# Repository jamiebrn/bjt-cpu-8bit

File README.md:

# BJT 8 bit CPU

Designing and (hopefully) building a custom 8 bit CPU with NPN bipolar junction transistors

The [ISA](specification.txt) is fully working and implemented in [logisim](logisim-prototypes/cpu-rebuild.circ), as shown:

I have also written an [assembler](assembler/assembler.cpp), and am working on the [emulator](emulator/) (functional but some graphics issues).

A barebones [standard library](programs/stdlib/) is also implemented.

## Physical build
I have [prototyped the ALU on breadboards](images/8bit-alu-labelled.png), and have started [working on PCB components](images/pcb-8bit-reg-v3-refined.png).

### "Just use ICs"
No

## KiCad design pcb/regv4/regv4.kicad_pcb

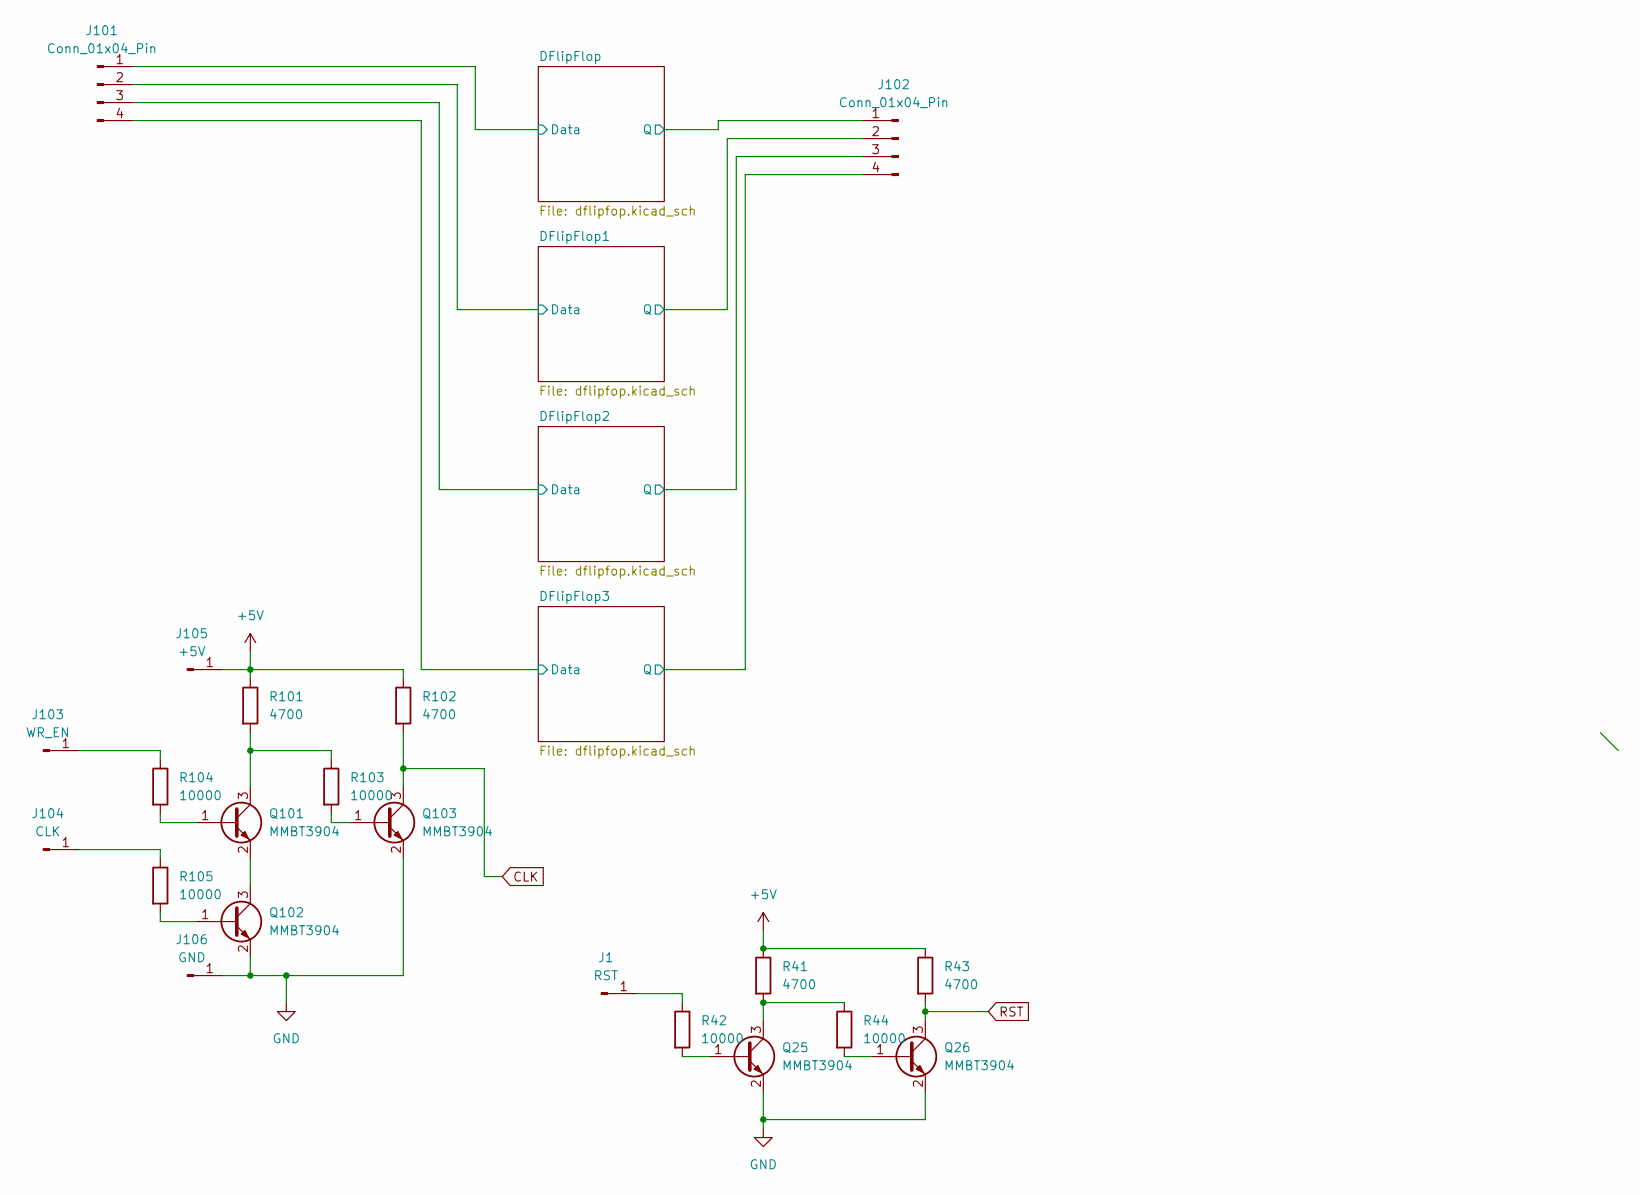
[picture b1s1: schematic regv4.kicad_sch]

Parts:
J1: RST; PinHeader_1x01_P2.54mm_Vertical
J101, J102: Conn_01x04_Pin; PinHeader_1x04_P2.54mm_Vertical
J103: WR_EN; PinHeader_1x01_P2.54mm_Vertical
J104: CLK; PinHeader_1x01_P2.54mm_Vertical
J105: +5V; PinHeader_1x01_P2.54mm_Vertical
J106: GND; PinHeader_1x01_P2.54mm_Vertical
Q25, Q26, Q101, Q102, Q103: MMBT3904; SOT-23
R41, R43, R101, R102: 4700; R_0805_2012Metric
R42, R44, R103, R104, R105: 10000; R_0805_2012Metric

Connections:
+5V: J105.1, R41.1, R43.1, R101.1, R102.1; also elsewhere on the board
/DFlipFlop1/Data: J101.2; also elsewhere on the board
/DFlipFlop1/Q: J102.2; also elsewhere on the board
/DFlipFlop2/Data: J101.3; also elsewhere on the board
/DFlipFlop2/Q: J102.3; also elsewhere on the board
/DFlipFlop3/Data: J101.4; also elsewhere on the board
/DFlipFlop3/Q: J102.4; also elsewhere on the board
/DFlipFlop/Data: J101.1; also elsewhere on the board
/DFlipFlop/Q: J102.1; also elsewhere on the board
CLK: Q103.3 (C), R102.2; also elsewhere on the board
GND: J106.1, Q25.2 (E), Q26.2 (E), Q102.2 (E), Q103.2 (E); also elsewhere on the board
unnamed: J1.1, R42.1
unnamed: J103.1, R104.1
unnamed: J104.1, R105.1
unnamed: Q25.1 (B), R42.2
unnamed: Q25.3 (C), R41.2, R44.1
unnamed: Q26.1 (B), R44.2
unnamed: Q101.1 (B), R104.2
unnamed: Q101.3 (C), R101.2, R103.1
unnamed: Q101.2 (E), Q102.3 (C)
unnamed: Q102.1 (B), R105.2
unnamed: Q103.1 (B), R103.2
RST: Q26.3 (C), R43.2; also elsewhere on the board

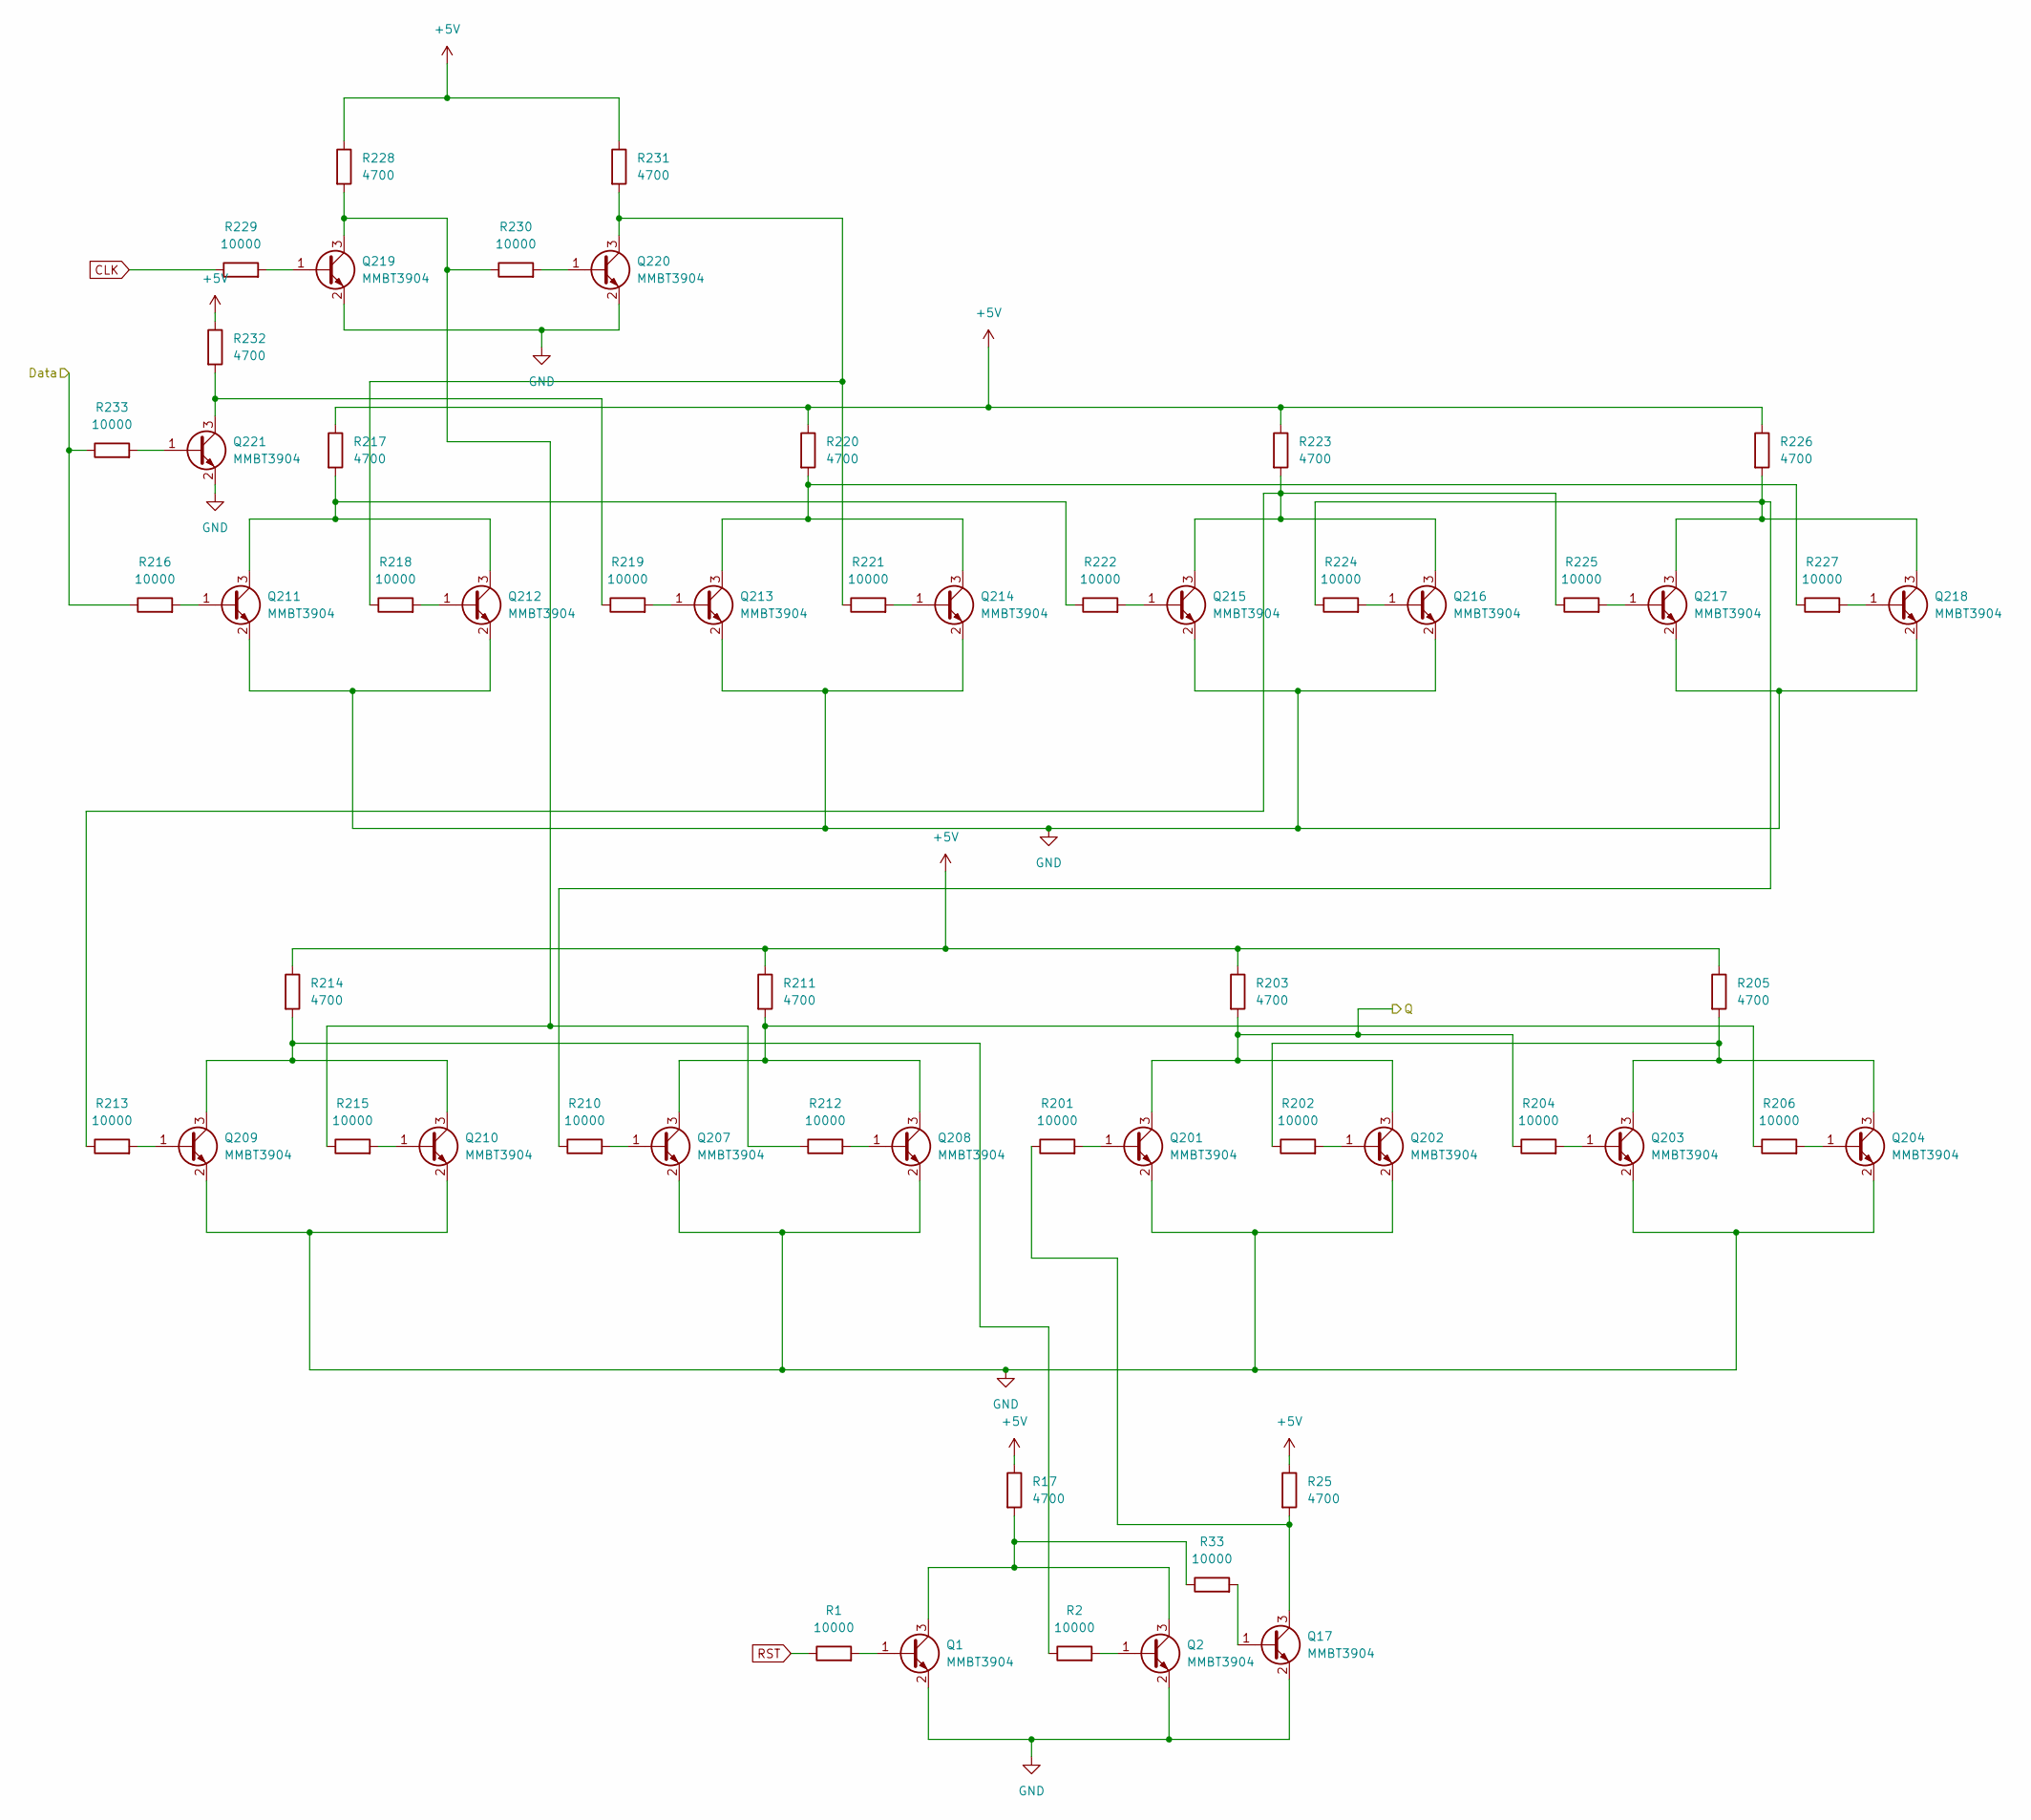
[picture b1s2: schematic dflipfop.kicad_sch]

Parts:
Q1, Q2, Q17, Q201, Q202, Q203, Q204, Q207, Q208, Q209, Q210, Q211, Q212, Q213, Q214, Q215, Q216, Q217, Q218, Q219, Q220, Q221: MMBT3904; SOT-23
R1, R2, R33, R201, R202, R204, R206, R210, R212, R213, R215, R216, R218, R219, R221, R222, R224, R225, R227, R229, R230, R233: 10000; R_0805_2012Metric
R17, R25, R203, R205, R211, R214, R217, R220, R223, R226, R228, R231, R232: 4700; R_0805_2012Metric

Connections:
+5V: R17.1, R25.1, R203.1, R205.1, R211.1, R214.1, R217.1, R220.1, R223.1, R226.1, R228.1, R231.1, R232.1; also elsewhere on the board
/DFlipFlop/Data: R216.1, R233.1; also elsewhere on the board
/DFlipFlop/Q: Q201.3 (C), Q202.3 (C), R203.2, R204.1; also elsewhere on the board
CLK: R229.1; also elsewhere on the board
GND: Q1.2 (E), Q2.2 (E), Q17.2 (E), Q201.2 (E), Q202.2 (E), Q203.2 (E), Q204.2 (E), Q207.2 (E), Q208.2 (E), Q209.2 (E), Q210.2 (E), Q211.2 (E), Q212.2 (E), Q213.2 (E), Q214.2 (E), Q215.2 (E), Q216.2 (E), Q217.2 (E), Q218.2 (E), Q219.2 (E), Q220.2 (E), Q221.2 (E); also elsewhere on the board
unnamed: Q1.1 (B), R1.2
unnamed: Q1.3 (C), Q2.3 (C), R17.2, R33.1
unnamed: Q2.1 (B), R2.2
unnamed: Q17.1 (B), R33.2
unnamed: Q17.3 (C), R25.2, R201.1
unnamed: Q201.1 (B), R201.2
unnamed: Q202.1 (B), R202.2
unnamed: Q203.1 (B), R204.2
unnamed: Q203.3 (C), Q204.3 (C), R202.1, R205.2
unnamed: Q204.1 (B), R206.2
unnamed: Q207.1 (B), R210.2
unnamed: Q207.3 (C), Q208.3 (C), R206.1, R211.2
unnamed: Q208.1 (B), R212.2
unnamed: Q209.1 (B), R213.2
unnamed: Q209.3 (C), Q210.3 (C), R2.1, R214.2
unnamed: Q210.1 (B), R215.2
unnamed: Q211.1 (B), R216.2
unnamed: Q211.3 (C), Q212.3 (C), R217.2, R222.1
unnamed: Q212.1 (B), R218.2
unnamed: Q213.1 (B), R219.2
unnamed: Q213.3 (C), Q214.3 (C), R220.2, R227.1
unnamed: Q214.1 (B), R221.2
unnamed: Q215.1 (B), R222.2
unnamed: Q215.3 (C), Q216.3 (C), R213.1, R223.2, R225.1
unnamed: Q216.1 (B), R224.2
unnamed: Q217.1 (B), R225.2
unnamed: Q217.3 (C), Q218.3 (C), R210.1, R224.1, R226.2
unnamed: Q218.1 (B), R227.2
unnamed: Q219.1 (B), R229.2
unnamed: Q219.3 (C), R212.1, R215.1, R228.2, R230.1
unnamed: Q220.1 (B), R230.2
unnamed: Q220.3 (C), R218.1, R221.1, R231.2
unnamed: Q221.1 (B), R233.2
unnamed: Q221.3 (C), R219.1, R232.2
RST: R1.1; also elsewhere on the board

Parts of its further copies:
Q3, Q4, Q5, Q6, Q7, Q8, Q18, Q19, Q20, Q301, Q302, Q303, Q304, Q305, Q306, Q307, Q308, Q309, Q310, Q311, Q312, Q313, Q314, Q315, Q316, Q317, Q318, Q319, Q401, Q402, Q403, Q404, Q405, Q406, Q407, Q408, Q409, Q410, Q411, Q412, Q413, Q414, Q415, Q416, Q417, Q418, Q419, Q501, Q502, Q503, Q504, Q505, Q506, Q507, Q508, Q509, Q510, Q511, Q512, Q513, Q514, Q515, Q516, Q517, Q518, Q519: MMBT3904; SOT-23
R3, R4, R5, R6, R7, R8, R34, R35, R36, R301, R302, R303, R305, R309, R310, R311, R312, R314, R317, R318, R319, R320, R323, R324, R325, R326, R329, R330, R401, R402, R403, R405, R409, R410, R411, R412, R414, R417, R418, R419, R420, R423, R424, R425, R426, R429, R430, R501, R502, R503, R505, R509, R510, R511, R512, R514, R517, R518, R519, R520, R523, R524, R525, R526, R529, R530: 10000; R_0805_2012Metric
R18, R19, R20, R26, R27, R28, R304, R306, R307, R308, R313, R315, R316, R321, R322, R327, R328, R404, R406, R407, R408, R413, R415, R416, R421, R422, R427, R428, R504, R506, R507, R508, R513, R515, R516, R521, R522, R527, R528: 4700; R_0805_2012Metric

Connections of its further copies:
+5V: R18.1, R19.1, R20.1, R26.1, R27.1, R28.1, R304.1, R306.1, R307.1, R308.1, R313.1, R315.1, R316.1, R321.1, R322.1, R327.1, R328.1, R404.1, R406.1, R407.1, R408.1, R413.1, R415.1, R416.1, R421.1, R422.1, R427.1, R428.1, R504.1, R506.1, R507.1, R508.1, R513.1, R515.1, R516.1, R521.1, R522.1, R527.1, R528.1; also elsewhere on the board
/DFlipFlop1/Data: R301.1, R303.1; also elsewhere on the board
/DFlipFlop1/Q: Q312.3 (C), Q314.3 (C), R321.2, R325.1; also elsewhere on the board
/DFlipFlop2/Data: R401.1, R403.1; also elsewhere on the board
/DFlipFlop2/Q: Q412.3 (C), Q414.3 (C), R421.2, R425.1; also elsewhere on the board
/DFlipFlop3/Data: R501.1, R503.1; also elsewhere on the board
/DFlipFlop3/Q: Q512.3 (C), Q514.3 (C), R521.2, R525.1; also elsewhere on the board
CLK: R305.1, R405.1, R505.1; also elsewhere on the board
GND: Q3.2 (E), Q4.2 (E), Q5.2 (E), Q6.2 (E), Q7.2 (E), Q8.2 (E), Q18.2 (E), Q19.2 (E), Q20.2 (E), Q301.2 (E), Q302.2 (E), Q303.2 (E), Q304.2 (E), Q305.2 (E), Q306.2 (E), Q307.2 (E), Q308.2 (E), Q309.2 (E), Q310.2 (E), Q311.2 (E), Q312.2 (E), Q313.2 (E), Q314.2 (E), Q315.2 (E), Q316.2 (E), Q317.2 (E), Q318.2 (E), Q319.2 (E), Q401.2 (E), Q402.2 (E), Q403.2 (E), Q404.2 (E), Q405.2 (E), Q406.2 (E), Q407.2 (E), Q408.2 (E), Q409.2 (E), Q410.2 (E), Q411.2 (E), Q412.2 (E), Q413.2 (E), Q414.2 (E), Q415.2 (E), Q416.2 (E), Q417.2 (E), Q418.2 (E), Q419.2 (E), Q501.2 (E), Q502.2 (E), Q503.2 (E), Q504.2 (E), Q505.2 (E), Q506.2 (E), Q507.2 (E), Q508.2 (E), Q509.2 (E), Q510.2 (E), Q511.2 (E), Q512.2 (E), Q513.2 (E), Q514.2 (E), Q515.2 (E), Q516.2 (E), Q517.2 (E), Q518.2 (E), Q519.2 (E); also elsewhere on the board
unnamed: Q3.1 (B), R3.2
unnamed: Q3.3 (C), Q4.3 (C), R18.2, R34.1
unnamed: Q4.1 (B), R4.2
unnamed: Q5.1 (B), R5.2
unnamed: Q5.3 (C), Q6.3 (C), R19.2, R35.1
unnamed: Q6.1 (B), R6.2
unnamed: Q7.1 (B), R7.2
unnamed: Q7.3 (C), Q8.3 (C), R20.2, R36.1
unnamed: Q8.1 (B), R8.2
unnamed: Q18.1 (B), R34.2
unnamed: Q18.3 (C), R26.2, R319.1
unnamed: Q19.1 (B), R35.2
unnamed: Q19.3 (C), R27.2, R419.1
unnamed: Q20.1 (B), R36.2
unnamed: Q20.3 (C), R28.2, R519.1
unnamed: Q301.1 (B), R302.2
unnamed: Q301.3 (C), Q305.3 (C), R4.1, R306.2
unnamed: Q302.1 (B), R301.2
unnamed: Q302.3 (C), R304.2, R314.1
unnamed: Q303.1 (B), R303.2
unnamed: Q303.3 (C), Q306.3 (C), R307.2, R320.1
unnamed: Q304.1 (B), R305.2
unnamed: Q304.3 (C), R308.2, R309.1, R311.1, R317.1
unnamed: Q305.1 (B), R309.2
unnamed: Q306.1 (B), R310.2
unnamed: Q307.1 (B), R311.2
unnamed: Q307.3 (C), R310.1, R313.2, R318.1
unnamed: Q308.1 (B), R312.2
unnamed: Q308.3 (C), Q310.3 (C), R315.2, R329.1
unnamed: Q309.1 (B), R314.2
unnamed: Q309.3 (C), Q311.3 (C), R316.2, R330.1
unnamed: Q310.1 (B), R317.2
unnamed: Q311.1 (B), R318.2
unnamed: Q312.1 (B), R319.2
unnamed: Q313.1 (B), R320.2
unnamed: Q313.3 (C), Q315.3 (C), R302.1, R322.2, R326.1
unnamed: Q314.1 (B), R323.2
unnamed: Q315.1 (B), R324.2
unnamed: Q316.1 (B), R325.2
unnamed: Q316.3 (C), Q318.3 (C), R323.1, R327.2
unnamed: Q317.1 (B), R326.2
unnamed: Q317.3 (C), Q319.3 (C), R312.1, R324.1, R328.2
unnamed: Q318.1 (B), R329.2
unnamed: Q319.1 (B), R330.2
unnamed: Q401.1 (B), R402.2
unnamed: Q401.3 (C), Q405.3 (C), R6.1, R406.2
unnamed: Q402.1 (B), R401.2
unnamed: Q402.3 (C), R404.2, R414.1
unnamed: Q403.1 (B), R403.2
unnamed: Q403.3 (C), Q406.3 (C), R407.2, R420.1
unnamed: Q404.1 (B), R405.2
unnamed: Q404.3 (C), R408.2, R409.1, R411.1, R417.1
unnamed: Q405.1 (B), R409.2
unnamed: Q406.1 (B), R410.2
unnamed: Q407.1 (B), R411.2
unnamed: Q407.3 (C), R410.1, R413.2, R418.1
unnamed: Q408.1 (B), R412.2
unnamed: Q408.3 (C), Q410.3 (C), R415.2, R429.1
unnamed: Q409.1 (B), R414.2
unnamed: Q409.3 (C), Q411.3 (C), R416.2, R430.1
unnamed: Q410.1 (B), R417.2
unnamed: Q411.1 (B), R418.2
unnamed: Q412.1 (B), R419.2
unnamed: Q413.1 (B), R420.2
unnamed: Q413.3 (C), Q415.3 (C), R402.1, R422.2, R426.1
unnamed: Q414.1 (B), R423.2
unnamed: Q415.1 (B), R424.2
unnamed: Q416.1 (B), R425.2
unnamed: Q416.3 (C), Q418.3 (C), R423.1, R427.2
unnamed: Q417.1 (B), R426.2
unnamed: Q417.3 (C), Q419.3 (C), R412.1, R424.1, R428.2
unnamed: Q418.1 (B), R429.2
unnamed: Q419.1 (B), R430.2
unnamed: Q501.1 (B), R502.2
unnamed: Q501.3 (C), Q505.3 (C), R8.1, R506.2
unnamed: Q502.1 (B), R501.2
unnamed: Q502.3 (C), R504.2, R514.1
unnamed: Q503.1 (B), R503.2
unnamed: Q503.3 (C), Q506.3 (C), R507.2, R520.1
unnamed: Q504.1 (B), R505.2
unnamed: Q504.3 (C), R508.2, R509.1, R511.1, R517.1
unnamed: Q505.1 (B), R509.2
unnamed: Q506.1 (B), R510.2
unnamed: Q507.1 (B), R511.2
unnamed: Q507.3 (C), R510.1, R513.2, R518.1
unnamed: Q508.1 (B), R512.2
unnamed: Q508.3 (C), Q510.3 (C), R515.2, R529.1
unnamed: Q509.1 (B), R514.2
unnamed: Q509.3 (C), Q511.3 (C), R516.2, R530.1
unnamed: Q510.1 (B), R517.2
unnamed: Q511.1 (B), R518.2
unnamed: Q512.1 (B), R519.2
unnamed: Q513.1 (B), R520.2
unnamed: Q513.3 (C), Q515.3 (C), R502.1, R522.2, R526.1
unnamed: Q514.1 (B), R523.2
unnamed: Q515.1 (B), R524.2
unnamed: Q516.1 (B), R525.2
unnamed: Q516.3 (C), Q518.3 (C), R523.1, R527.2
unnamed: Q517.1 (B), R526.2
unnamed: Q517.3 (C), Q519.3 (C), R512.1, R524.1, R528.2
unnamed: Q518.1 (B), R529.2
unnamed: Q519.1 (B), R530.2
RST: R3.1, R5.1, R7.1; also elsewhere on the board

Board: 4 copper layers, 249 parts (0 on the bottom side), 159 nets, no tracks yet.

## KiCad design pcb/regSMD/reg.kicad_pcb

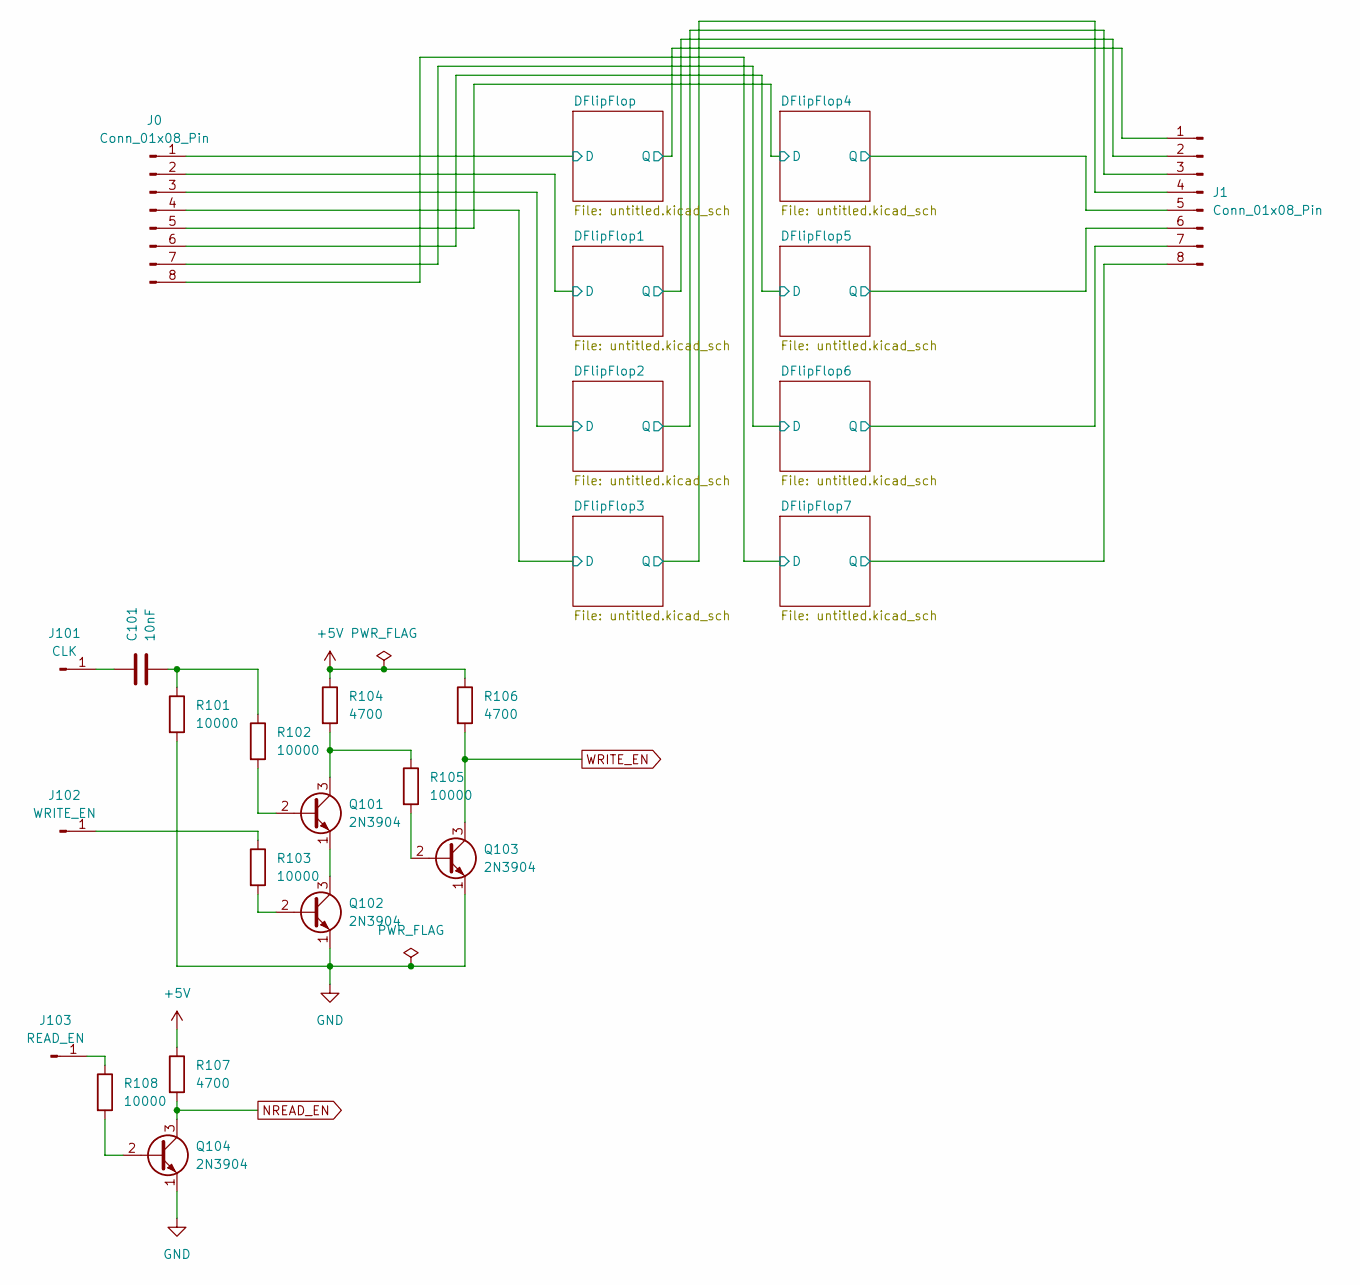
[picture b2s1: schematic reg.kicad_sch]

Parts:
C101: 10nF; C_Disc_D5.0mm_W2.5mm_P5.00mm
J0, J1: Conn_01x08_Pin; PinHeader_1x08_P2.54mm_Vertical
J101: CLK
J102: WRITE_EN; PinHeader_1x01_P2.54mm_Vertical
J103: READ_EN; PinHeader_1x01_P2.54mm_Vertical
Q101, Q102, Q103, Q104: 2N3904; TO-92_Inline
R101, R102, R103, R105, R108: 10000; R_0805_2012Metric
R104, R106, R107: 4700; R_0805_2012Metric

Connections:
+5V: R104.1, R106.1, R107.1; also elsewhere on the board
GND: Q102.1 (E), Q103.1 (E), Q104.1 (E), R101.2; also elsewhere on the board
NREAD_EN: Q104.3 (C), R107.2; also elsewhere on the board
unnamed: C101.2, R101.1, R102.1
unnamed 20: C101.1, J101.1; also elsewhere on the board
unnamed 21: J102.1, R103.1; also elsewhere on the board
unnamed 22: J103.1, R108.1; also elsewhere on the board
unnamed: Q101.2 (B), R102.2
unnamed: Q101.3 (C), R104.2, R105.1
unnamed: Q101.1 (E), Q102.3 (C)
unnamed: Q102.2 (B), R103.2
unnamed: Q103.2 (B), R105.2
unnamed: Q104.2 (B), R108.2
WRITE_EN: Q103.3 (C), R106.2; also elsewhere on the board

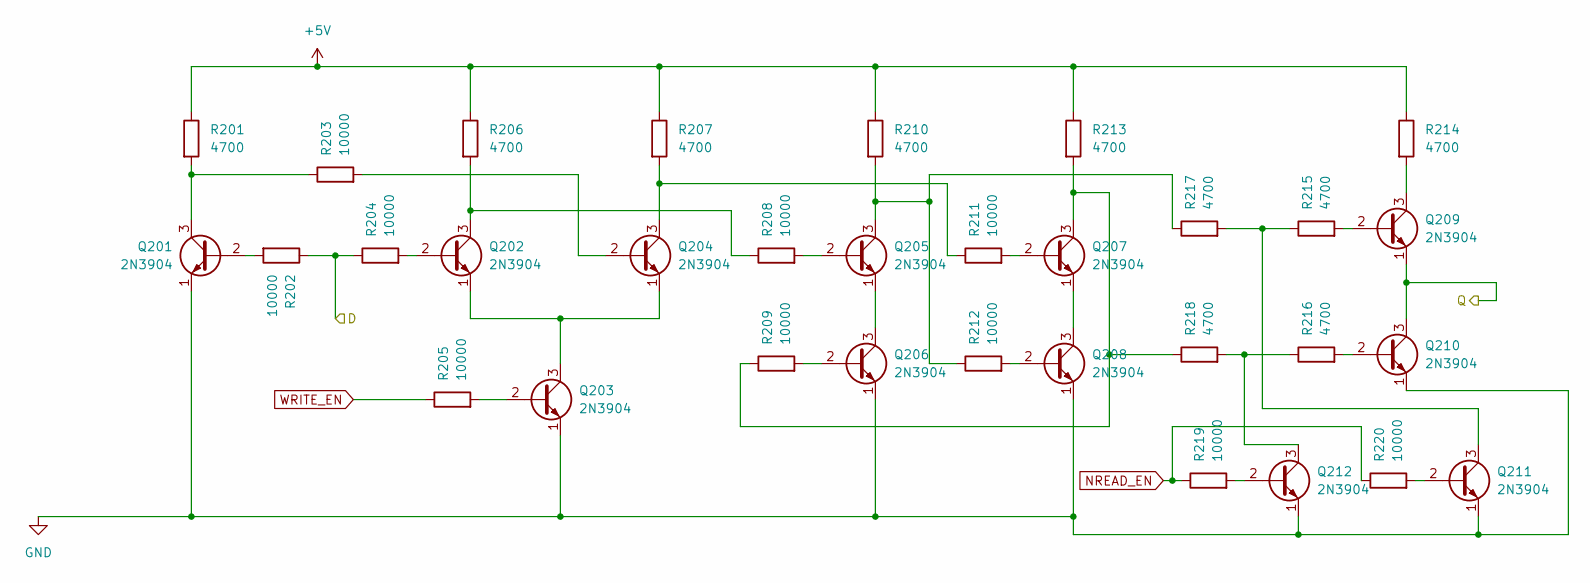
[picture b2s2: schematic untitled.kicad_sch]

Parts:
Q201, Q202, Q203, Q204, Q205, Q206, Q207, Q208, Q209, Q210, Q211, Q212: 2N3904; TO-92_Inline
R201, R206, R207, R210, R213, R214, R215, R216, R217, R218: 4700; R_0805_2012Metric
R202, R203, R204, R205, R208, R209, R211, R212, R219, R220: 10000; R_0805_2012Metric

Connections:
+5V: R201.1, R206.1, R207.1, R210.1, R213.1, R214.1; also elsewhere on the board
/DFlipFlop/D: R202.1, R204.1; also elsewhere on the board
/DFlipFlop/Q: Q209.1 (E), Q210.3 (C); also elsewhere on the board
GND: Q201.1 (E), Q203.1 (E), Q206.1 (E), Q208.1 (E), Q210.1 (E), Q211.1 (E), Q212.1 (E); also elsewhere on the board
NREAD_EN: R219.1, R220.1; also elsewhere on the board
unnamed: Q201.2 (B), R202.2
unnamed: Q201.3 (C), R201.2, R203.1
unnamed: Q202.2 (B), R204.2
unnamed: Q202.3 (C), R206.2, R208.1
unnamed: Q202.1 (E), Q203.3 (C), Q204.1 (E)
unnamed: Q203.2 (B), R205.2
unnamed: Q204.2 (B), R203.2
unnamed: Q204.3 (C), R207.2, R211.1
unnamed: Q205.2 (B), R208.2
unnamed: Q205.3 (C), R210.2, R212.1, R217.1
unnamed: Q205.1 (E), Q206.3 (C)
unnamed: Q206.2 (B), R209.2
unnamed: Q207.2 (B), R211.2
unnamed: Q207.3 (C), R209.1, R213.2, R218.1
unnamed: Q207.1 (E), Q208.3 (C)
unnamed: Q208.2 (B), R212.2
unnamed: Q209.2 (B), R215.2
unnamed: Q209.3 (C), R214.2
unnamed: Q210.2 (B), R216.2
unnamed: Q211.2 (B), R220.2
unnamed: Q211.3 (C), R215.1, R217.2
unnamed: Q212.2 (B), R219.2
unnamed: Q212.3 (C), R216.1, R218.2
WRITE_EN: R205.1; also elsewhere on the board

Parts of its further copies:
Q301, Q302, Q303, Q304, Q305, Q306, Q307, Q308, Q309, Q310, Q311, Q312, Q401, Q402, Q403, Q404, Q405, Q406, Q407, Q408, Q409, Q410, Q411, Q412, Q501, Q502, Q503, Q504, Q505, Q506, Q507, Q508, Q509, Q510, Q511, Q512, Q601, Q602, Q603, Q604, Q605, Q606, Q607, Q608, Q609, Q610, Q611, Q612, Q701, Q702, Q703, Q704, Q705, Q706, Q707, Q708, Q709, Q710, Q711, Q712, Q801, Q802, Q803, Q804, Q805, Q806, Q807, Q808, Q809, Q810, Q811, Q812, Q901, Q902, Q903, Q904, Q905, Q906, Q907, Q908, Q909, Q910, Q911, Q912: 2N3904; TO-92_Inline
R301, R306, R307, R310, R313, R314, R315, R316, R317, R318, R401, R406, R407, R410, R413, R414, R415, R416, R417, R418, R501, R506, R507, R510, R513, R514, R515, R516, R517, R518, R601, R606, R607, R610, R613, R614, R615, R616, R617, R618, R701, R706, R707, R710, R713, R714, R715, R716, R717, R718, R801, R806, R807, R810, R813, R814, R815, R816, R817, R818, R901, R906, R907, R910, R913, R914, R915, R916, R917, R918: 4700; R_0805_2012Metric
R302, R303, R304, R305, R308, R309, R311, R312, R319, R320, R402, R403, R404, R405, R408, R409, R411, R412, R419, R420, R502, R503, R504, R505, R508, R509, R511, R512, R519, R520, R602, R603, R604, R605, R608, R609, R611, R612, R619, R620, R702, R703, R704, R705, R708, R709, R711, R712, R719, R720, R802, R803, R804, R805, R808, R809, R811, R812, R819, R820, R902, R903, R904, R905, R908, R909, R911, R912, R919, R920: 10000; R_0805_2012Metric

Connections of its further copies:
+5V: R301.1, R306.1, R307.1, R310.1, R313.1, R314.1, R401.1, R406.1, R407.1, R410.1, R413.1, R414.1, R501.1, R506.1, R507.1, R510.1, R513.1, R514.1, R601.1, R606.1, R607.1, R610.1, R613.1, R614.1, R701.1, R706.1, R707.1, R710.1, R713.1, R714.1, R801.1, R806.1, R807.1, R810.1, R813.1, R814.1, R901.1, R906.1, R907.1, R910.1, R913.1, R914.1; also elsewhere on the board
/DFlipFlop1/D: R302.1, R304.1; also elsewhere on the board
/DFlipFlop1/Q: Q309.1 (E), Q310.3 (C); also elsewhere on the board
/DFlipFlop2/D: R402.1, R404.1; also elsewhere on the board
/DFlipFlop2/Q: Q409.1 (E), Q410.3 (C); also elsewhere on the board
/DFlipFlop3/D: R502.1, R504.1; also elsewhere on the board
/DFlipFlop3/Q: Q509.1 (E), Q510.3 (C); also elsewhere on the board
/DFlipFlop4/D: R602.1, R604.1; also elsewhere on the board
/DFlipFlop4/Q: Q609.1 (E), Q610.3 (C); also elsewhere on the board
/DFlipFlop5/D: R702.1, R704.1; also elsewhere on the board
/DFlipFlop5/Q: Q709.1 (E), Q710.3 (C); also elsewhere on the board
/DFlipFlop6/D: R802.1, R804.1; also elsewhere on the board
/DFlipFlop6/Q: Q809.1 (E), Q810.3 (C); also elsewhere on the board
/DFlipFlop7/D: R902.1, R904.1; also elsewhere on the board
/DFlipFlop7/Q: Q909.1 (E), Q910.3 (C); also elsewhere on the board
GND: Q301.1 (E), Q303.1 (E), Q306.1 (E), Q308.1 (E), Q310.1 (E), Q311.1 (E), Q312.1 (E), Q401.1 (E), Q403.1 (E), Q406.1 (E), Q408.1 (E), Q410.1 (E), Q411.1 (E), Q412.1 (E), Q501.1 (E), Q503.1 (E), Q506.1 (E), Q508.1 (E), Q510.1 (E), Q511.1 (E), Q512.1 (E), Q601.1 (E), Q603.1 (E), Q606.1 (E), Q608.1 (E), Q610.1 (E), Q611.1 (E), Q612.1 (E), Q701.1 (E), Q703.1 (E), Q706.1 (E), Q708.1 (E), Q710.1 (E), Q711.1 (E), Q712.1 (E), Q801.1 (E), Q803.1 (E), Q806.1 (E), Q808.1 (E), Q810.1 (E), Q811.1 (E), Q812.1 (E), Q901.1 (E), Q903.1 (E), Q906.1 (E), Q908.1 (E), Q910.1 (E), Q911.1 (E), Q912.1 (E); also elsewhere on the board
NREAD_EN: R319.1, R320.1, R419.1, R420.1, R519.1, R520.1, R619.1, R620.1, R719.1, R720.1, R819.1, R820.1, R919.1, R920.1; also elsewhere on the board
unnamed: Q301.2 (B), R302.2
unnamed: Q301.3 (C), R301.2, R303.1
unnamed: Q302.2 (B), R304.2
unnamed: Q302.3 (C), R306.2, R308.1
unnamed: Q302.1 (E), Q303.3 (C), Q304.1 (E)
unnamed: Q303.2 (B), R305.2
unnamed: Q304.2 (B), R303.2
unnamed: Q304.3 (C), R307.2, R311.1
unnamed: Q305.2 (B), R308.2
unnamed: Q305.3 (C), R310.2, R312.1, R317.1
unnamed: Q305.1 (E), Q306.3 (C)
unnamed: Q306.2 (B), R309.2
unnamed: Q307.2 (B), R311.2
unnamed: Q307.3 (C), R309.1, R313.2, R318.1
unnamed: Q307.1 (E), Q308.3 (C)
unnamed: Q308.2 (B), R312.2
unnamed: Q309.2 (B), R315.2
unnamed: Q309.3 (C), R314.2
unnamed: Q310.2 (B), R316.2
unnamed: Q311.2 (B), R320.2
unnamed: Q311.3 (C), R315.1, R317.2
unnamed: Q312.2 (B), R319.2
unnamed: Q312.3 (C), R316.1, R318.2
unnamed: Q401.2 (B), R402.2
unnamed: Q401.3 (C), R401.2, R403.1
unnamed: Q402.2 (B), R404.2
unnamed: Q402.3 (C), R406.2, R408.1
unnamed: Q402.1 (E), Q403.3 (C), Q404.1 (E)
unnamed: Q403.2 (B), R405.2
unnamed: Q404.2 (B), R403.2
unnamed: Q404.3 (C), R407.2, R411.1
unnamed: Q405.2 (B), R408.2
unnamed: Q405.3 (C), R410.2, R412.1, R417.1
unnamed: Q405.1 (E), Q406.3 (C)
unnamed: Q406.2 (B), R409.2
unnamed: Q407.2 (B), R411.2
unnamed: Q407.3 (C), R409.1, R413.2, R418.1
unnamed: Q407.1 (E), Q408.3 (C)
unnamed: Q408.2 (B), R412.2
unnamed: Q409.2 (B), R415.2
unnamed: Q409.3 (C), R414.2
unnamed: Q410.2 (B), R416.2
unnamed: Q411.2 (B), R420.2
unnamed: Q411.3 (C), R415.1, R417.2
unnamed: Q412.2 (B), R419.2
unnamed: Q412.3 (C), R416.1, R418.2
unnamed: Q501.2 (B), R502.2
unnamed: Q501.3 (C), R501.2, R503.1
unnamed: Q502.2 (B), R504.2
unnamed: Q502.3 (C), R506.2, R508.1
unnamed: Q502.1 (E), Q503.3 (C), Q504.1 (E)
unnamed: Q503.2 (B), R505.2
unnamed: Q504.2 (B), R503.2
unnamed: Q504.3 (C), R507.2, R511.1
unnamed: Q505.2 (B), R508.2
unnamed: Q505.3 (C), R510.2, R512.1, R517.1
unnamed: Q505.1 (E), Q506.3 (C)
unnamed: Q506.2 (B), R509.2
unnamed: Q507.2 (B), R511.2
unnamed: Q507.3 (C), R509.1, R513.2, R518.1
unnamed: Q507.1 (E), Q508.3 (C)
unnamed: Q508.2 (B), R512.2
unnamed: Q509.2 (B), R515.2
unnamed: Q509.3 (C), R514.2
unnamed: Q510.2 (B), R516.2
unnamed: Q511.2 (B), R520.2
unnamed: Q511.3 (C), R515.1, R517.2
unnamed: Q512.2 (B), R519.2
unnamed: Q512.3 (C), R516.1, R518.2
unnamed: Q601.2 (B), R602.2
unnamed: Q601.3 (C), R601.2, R603.1
unnamed: Q602.2 (B), R604.2
unnamed: Q602.3 (C), R606.2, R608.1
unnamed: Q602.1 (E), Q603.3 (C), Q604.1 (E)
unnamed: Q603.2 (B), R605.2
unnamed: Q604.2 (B), R603.2
unnamed: Q604.3 (C), R607.2, R611.1
unnamed: Q605.2 (B), R608.2
unnamed: Q605.3 (C), R610.2, R612.1, R617.1
unnamed: Q605.1 (E), Q606.3 (C)
unnamed: Q606.2 (B), R609.2
unnamed: Q607.2 (B), R611.2
unnamed: Q607.3 (C), R609.1, R613.2, R618.1
unnamed: Q607.1 (E), Q608.3 (C)
unnamed: Q608.2 (B), R612.2
unnamed: Q609.2 (B), R615.2
unnamed: Q609.3 (C), R614.2
unnamed: Q610.2 (B), R616.2
unnamed: Q611.2 (B), R620.2
unnamed: Q611.3 (C), R615.1, R617.2
unnamed: Q612.2 (B), R619.2
unnamed: Q612.3 (C), R616.1, R618.2
unnamed: Q701.2 (B), R702.2
unnamed: Q701.3 (C), R701.2, R703.1
unnamed: Q702.2 (B), R704.2
unnamed: Q702.3 (C), R706.2, R708.1
unnamed: Q702.1 (E), Q703.3 (C), Q704.1 (E)
unnamed: Q703.2 (B), R705.2
unnamed: Q704.2 (B), R703.2
unnamed: Q704.3 (C), R707.2, R711.1
unnamed: Q705.2 (B), R708.2
unnamed: Q705.3 (C), R710.2, R712.1, R717.1
unnamed: Q705.1 (E), Q706.3 (C)
unnamed: Q706.2 (B), R709.2
unnamed: Q707.2 (B), R711.2
unnamed: Q707.3 (C), R709.1, R713.2, R718.1
unnamed: Q707.1 (E), Q708.3 (C)
unnamed: Q708.2 (B), R712.2
unnamed: Q709.2 (B), R715.2
unnamed: Q709.3 (C), R714.2
unnamed: Q710.2 (B), R716.2
unnamed: Q711.2 (B), R720.2
unnamed: Q711.3 (C), R715.1, R717.2
unnamed: Q712.2 (B), R719.2
unnamed: Q712.3 (C), R716.1, R718.2
unnamed: Q801.2 (B), R802.2
unnamed: Q801.3 (C), R801.2, R803.1
unnamed: Q802.2 (B), R804.2
unnamed: Q802.3 (C), R806.2, R808.1
unnamed: Q802.1 (E), Q803.3 (C), Q804.1 (E)
unnamed: Q803.2 (B), R805.2
unnamed: Q804.2 (B), R803.2
unnamed: Q804.3 (C), R807.2, R811.1
unnamed: Q805.2 (B), R808.2
unnamed: Q805.3 (C), R810.2, R812.1, R817.1
unnamed: Q805.1 (E), Q806.3 (C)
unnamed: Q806.2 (B), R809.2
unnamed: Q807.2 (B), R811.2
unnamed: Q807.3 (C), R809.1, R813.2, R818.1
unnamed: Q807.1 (E), Q808.3 (C)
unnamed: Q808.2 (B), R812.2
unnamed: Q809.2 (B), R815.2
unnamed: Q809.3 (C), R814.2
unnamed: Q810.2 (B), R816.2
unnamed: Q811.2 (B), R820.2
unnamed: Q811.3 (C), R815.1, R817.2
unnamed: Q812.2 (B), R819.2
unnamed: Q812.3 (C), R816.1, R818.2
unnamed: Q901.2 (B), R902.2
unnamed: Q901.3 (C), R901.2, R903.1
unnamed: Q902.2 (B), R904.2
unnamed: Q902.3 (C), R906.2, R908.1
unnamed: Q902.1 (E), Q903.3 (C), Q904.1 (E)
unnamed: Q903.2 (B), R905.2
unnamed: Q904.2 (B), R903.2
unnamed: Q904.3 (C), R907.2, R911.1
unnamed: Q905.2 (B), R908.2
unnamed: Q905.3 (C), R910.2, R912.1, R917.1
unnamed: Q905.1 (E), Q906.3 (C)
unnamed: Q906.2 (B), R909.2
unnamed: Q907.2 (B), R911.2
unnamed: Q907.3 (C), R909.1, R913.2, R918.1
unnamed: Q907.1 (E), Q908.3 (C)
unnamed: Q908.2 (B), R912.2
unnamed: Q909.2 (B), R915.2
unnamed: Q909.3 (C), R914.2
unnamed: Q910.2 (B), R916.2
unnamed: Q911.2 (B), R920.2
unnamed: Q911.3 (C), R915.1, R917.2
unnamed: Q912.2 (B), R919.2
unnamed: Q912.3 (C), R916.1, R918.2
WRITE_EN: R305.1, R405.1, R505.1, R605.1, R705.1, R805.1, R905.1; also elsewhere on the board
